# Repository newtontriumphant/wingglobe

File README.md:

# WingGlobe

Quick Link Tree:

* [I. Introduction!](#i-introduction)
* [II. About This Project - Why I Chose To Make It!](#ii-about-this-project---why-i-chose-to-make-it)
* [III. About This Project - What Is It?!](#iii-about-this-project---what-is-it)
* [IV. Project Images And Technical Documentation!](#iv-project-images-and-technical-documentation)
* [V. Notes For Reviewers!](#v-notes-for-reviewers)
* [VI. Final Remarks!](#vi-final-remarks)
  
## I. Introduction!

Heyo! Thanks for reviewing my project! I'm **zsharpminor** (a.k.a. funkeudo), co-creator of FiddleStein, and this is WingGlobe, which is a (TL;DR) fully autonomous Weather-Telling Snow Globe with a custom propulsion mechanism, PWM control, backlighting, E-INK display, support for my existing ecosystem of temperature sensors, and a changeable theme. This project is being created with the support of Hack Club Blueprint, and it is an entry for Blueprint's 7-day Christmas-Themed Project Competition. I am aiming for this to be a **Tier 3** project (see section at the very end of this README for justification).

(Disclaimer: the above image is a **render**, this project is not actually built yet; CAD screenshots can be found in section IV).

**IMPORTANT REVIEWER'S NOTE:** there is a section at the **end** of this README.md file, please read through it before returning this project if possible :)

My BOM.csv is in the parent directory, additionally a link to my online BOM is https://docs.google.com/spreadsheets/d/1PTxZxDy7cq01-oPVpPEEbVuQKtVb_WSBa-1fNMrsmt8/. Thanks! :3

Before I get into why I made this project, I would like to extend a huge thanks to can can't aka kleigh (my hero), as well as sam, alex, zach, renran, deven, paolo, john cohn, olive, my teammates Max & Sidd, tanuki, nathan, everyone from AMD, and every single other equally important person that made Blueprint & Prototype happen - I literally found out about Blueprint (and Hack Club itself!) only a month and a week ago, finished a few projects and became a reviewer one week later, had the most fun I've _ever_ had at Prototype, as well as inspired myself to get back into hardware, and re-dedicate my life to electronics. I really appreciate everything each and every one of you has done, and, without further ado, here's why WingGlobe exists.

## II. About This Project - Why I Chose To Make It!

You're probably looking at this and asking me "why the hell would you make a smart snow globe?!" The answer is a bit more complex than you think!

To start off with, I'm going to say quite bluntly that this project wouldn't exist without the Blueprint Christmas Competition. Even though I've worked with hardware for years, got HM with a self playing violin, and have been a Blueprint reviewer for over a month, I **don't actually own a 3D printer** (I've been using my local library's for all of my past projects so far)! I was planning on buying one a few weeks ago, then I set myself the challenge of getting one through Blueprint by reviewing a lot and getting tickets - but my current pace is rather lackluster. In addition, I needed ideas for projects to build - Blueprint is awesome because you can ship literally anything you can imagine, as long as it's under a certain dollar amount; but I was facing a bit of a creative block until this competition came about! My first project idea was to make a laser projecting 2026 New Year's countdown - but then I remembered that New Years would be over by the time this project would be built! My goal with WingGlobe was to make a project that, while Christmas-themed, **doesn't rely on Christmas to exist** and can be used **at any time of the year**! (Christmas in July, anyone?)

Additionally, I've made an ecosystem of projects (including one that I made through Blueprint - my SmartBell!) that feature temperature and humidity sensors. I wanted them to seamlessly work together wirelessly somehow, and needed a way to make that possible. That is also the main reason I chose the ESP32-S3 for this project, besides the fact that I already owned one, that it would cut PCBA cost in half, and that it would require one less parcel to be shipped.

Finally, I've been interested in weather and meteorology in general for a few years now, and I always wanted a weather station that relied on multiple sources of data that I myself provide, in addition to the commercial weather reports available.

The Snow Globe that builds this project's core features an empty space for _any_ 3d model or figurine (assuming it's heavy enough to withstand the fan blowing snow around it!) - and I've chosen a Christmas-themed one for my first few months with WingGlobe to fit the competition's theme.

Finally, if you're wondering why it's called WingGlobe, it's a reference to aviation, where meteorology is key (bad name, I know, but it stuck!)

I wanted WingGlobe to fit these criteria:

* It **must** be overwhelmingly Christmas-themed.
* It **must** have a decent amount of hardware complexity.
* It **must** be usable outside of just Christmas season.
* It **must** predominantly integrate CAD and software instead of being _just_ hardware.
* It **must** be actually useful in everyday life.
* The PCB **must** be under 100x100mm, eligible for GSDL, and Economic PCBA.
* All parts of the project **must** be printable on the Bambu A1 Mini with minimal supports and t*nkering.

I think I did a pretty good job fitting these criteria, if I do say so myself. Anyways, enough yapping, here's what the project actually _does_:

## III. About This Project - What Is It?!

WingGlobe is basically a glorified weather report station powered by a SEEED Studios XIAO ESP-32-S3 (that I already own - more on that in Section V) that runs 16 addressable SK6812-MINI LEDs, as well as an onboard temp/humi/pressure sensor and a MOSFET powering a 4010 fan with PWM control. When the weather shifts, the snow globe is updated to match - calm weather is a white / light-blue gradient and no fan power, sunny weather is a yellow / light red gradient, sunrise and sunset are adapted to red / orange gradients, and during the night, the snow globe will be engulfed in a replica of the aurora borealis (clear sky) or simply white / dark blue (cloudy sky). The real fun begins when it rains! When the winds start, the 4010 fan's PWM controller starts to rev it up - the more dangerous the wind, the more the little snow in the globe will swirl around! I am planning to use lightweight cotton / styrofoam blend beads to imitate snow (my original idea of 3D printing them sadly failed), as well as a custom mesh that stops them from breaking the fan or going out of the top of the globe. WingGlobe's E-Ink can be customized with a touch pad on WingGlobe's PCB to show varying levels of information from varying sensors. Additionally, the fan and LEDs can be turned off with a switch on WingGlobe's side when not needed (i.e. overnight).

WingGlobe seamlessly integrates with my SmartBell, moonboard, ADS-B stations, and BarnSense projects to provide up to three different simultaneous readings of temperature, humidity, and pressure. WingGlobe also has a built-in sensor for indoor temperature and humidity (should be quite useful next to my soon-to-be 3D Printer!) For now, WingGlobe relies on commercially available data for wind readings, but I hope to create another project soon so that everything can be run off the grid and without requiring any API.

WingGlobe's ESP32-S3 connects via ESP-NOW and WiFi to fetch data from my close and far stations, respectively. You're halfway there, have a cookie! 🍪

## IV. Project Images And Technical Documentation!

### SCHEMATIC:

### PCB:

### CAD:

(base, with cutouts for PCB, fan, and globe)

(top, made to be glued onto base)

### CAD WITH PCB:

(top view)

(side view)

(bottom view)

(top - birds-eye view without lid)

### ASSEMBLED PRODUCT:

(Front - Angle One)

(Front - Angle Two)

(Top)

(Side)

(Bottom)

### CARTS:

(AliExpress Checkout)

(JLCPCB PCB Options)

(JLCPCB PCBA 1)

(JLCPCB PCBA 2)

(JLCPCB PCBA 3)

(JLCPCB Pre-Discounts)

(JLCPCB Final Checkout As Shown On BOM)

**NOTE**: My name was redacted using the Inspect Element tool as this repository is publically visible. If an unredacted screenshot is required, please DM me or return my project.

### I will self-fund the E-INK display due to the project tier being bumped down to T4.

### RENDER:

(My friend with Blender skills did this and it turned out amazing, so I'm making this my cover image!)

## V. Notes For Reviewers!

### Usage Of Pre-Built Devboard:

I chose to use the XIAO ESP32-S3 over making a custom ESP32 or RP2040 devboard base for three reasons:

1. I already own quite a few ESP32-S3s, making an ESP32 from scratch would more than **double** the PCBA cost at JLC, and make my order **ineligible** for GSDL shipping, which would push my budget to Tier 2.
2. I've already made a devboard, I know the hassles that are involved in wiring and routing, and I did not want to miss a single decoupling capacitor and risk my board being browned out.
3. I wanted to spend more time polishing software and CAD, and using a pre-built devboard gave me that opportunity.

Again, if this cannot be approved for Tier 3 due to a lack of complexity, I understand, and will remove parts to bring the budget down to a Tier 4.

### Why Are You Requesting Six Snow Globes?

Because it's the cheapest option available for a half-decent snowglobe on AliExpress. The next-cheapest was $7 for two, and I preferred to get six for $6.88.

All of my costs are optimized as **much as possible**, I'm using AliExpress for my items, and I've done my best to keep it in budget.

### Why Are You Requesting $10 More Than You Need For JLCPCB?

JLCPCB has a $10 coupon for PCBA (scroll up to the images section for proof). Said coupon expires in 2 days, and, knowing HCB, it will take more than 2 days to process this grant. If another coupon appears, I will return the difference immediately.

### "ThIs ReADmE iS AI gEnEraTEd!"

No, no it's not. I know how to use markdown, and I'll even occasionally use an em-dash—like so. That doesn't necessarily mean my README is automatically AI. Zero AI was used in the making of this project, and writing this text-heavy README alone took me two hours. If you need proof, I can provide a screen recording!

That's all, thanks! :D

## VI. Final Remarks!

Please ping or DM me on Slack (@zsharpminor) if you have any questions regarding my project.

Thank you so much for taking your precious time to read all the way through this extremely long README (I wanted to be well documented, okay?!)

You get a massive slice of vanilla cheesecake! :D 🍰

P.S. Happy New Year!!! I worked on this project literally as the clock struck 12 - I have a journal entry to prove it :)

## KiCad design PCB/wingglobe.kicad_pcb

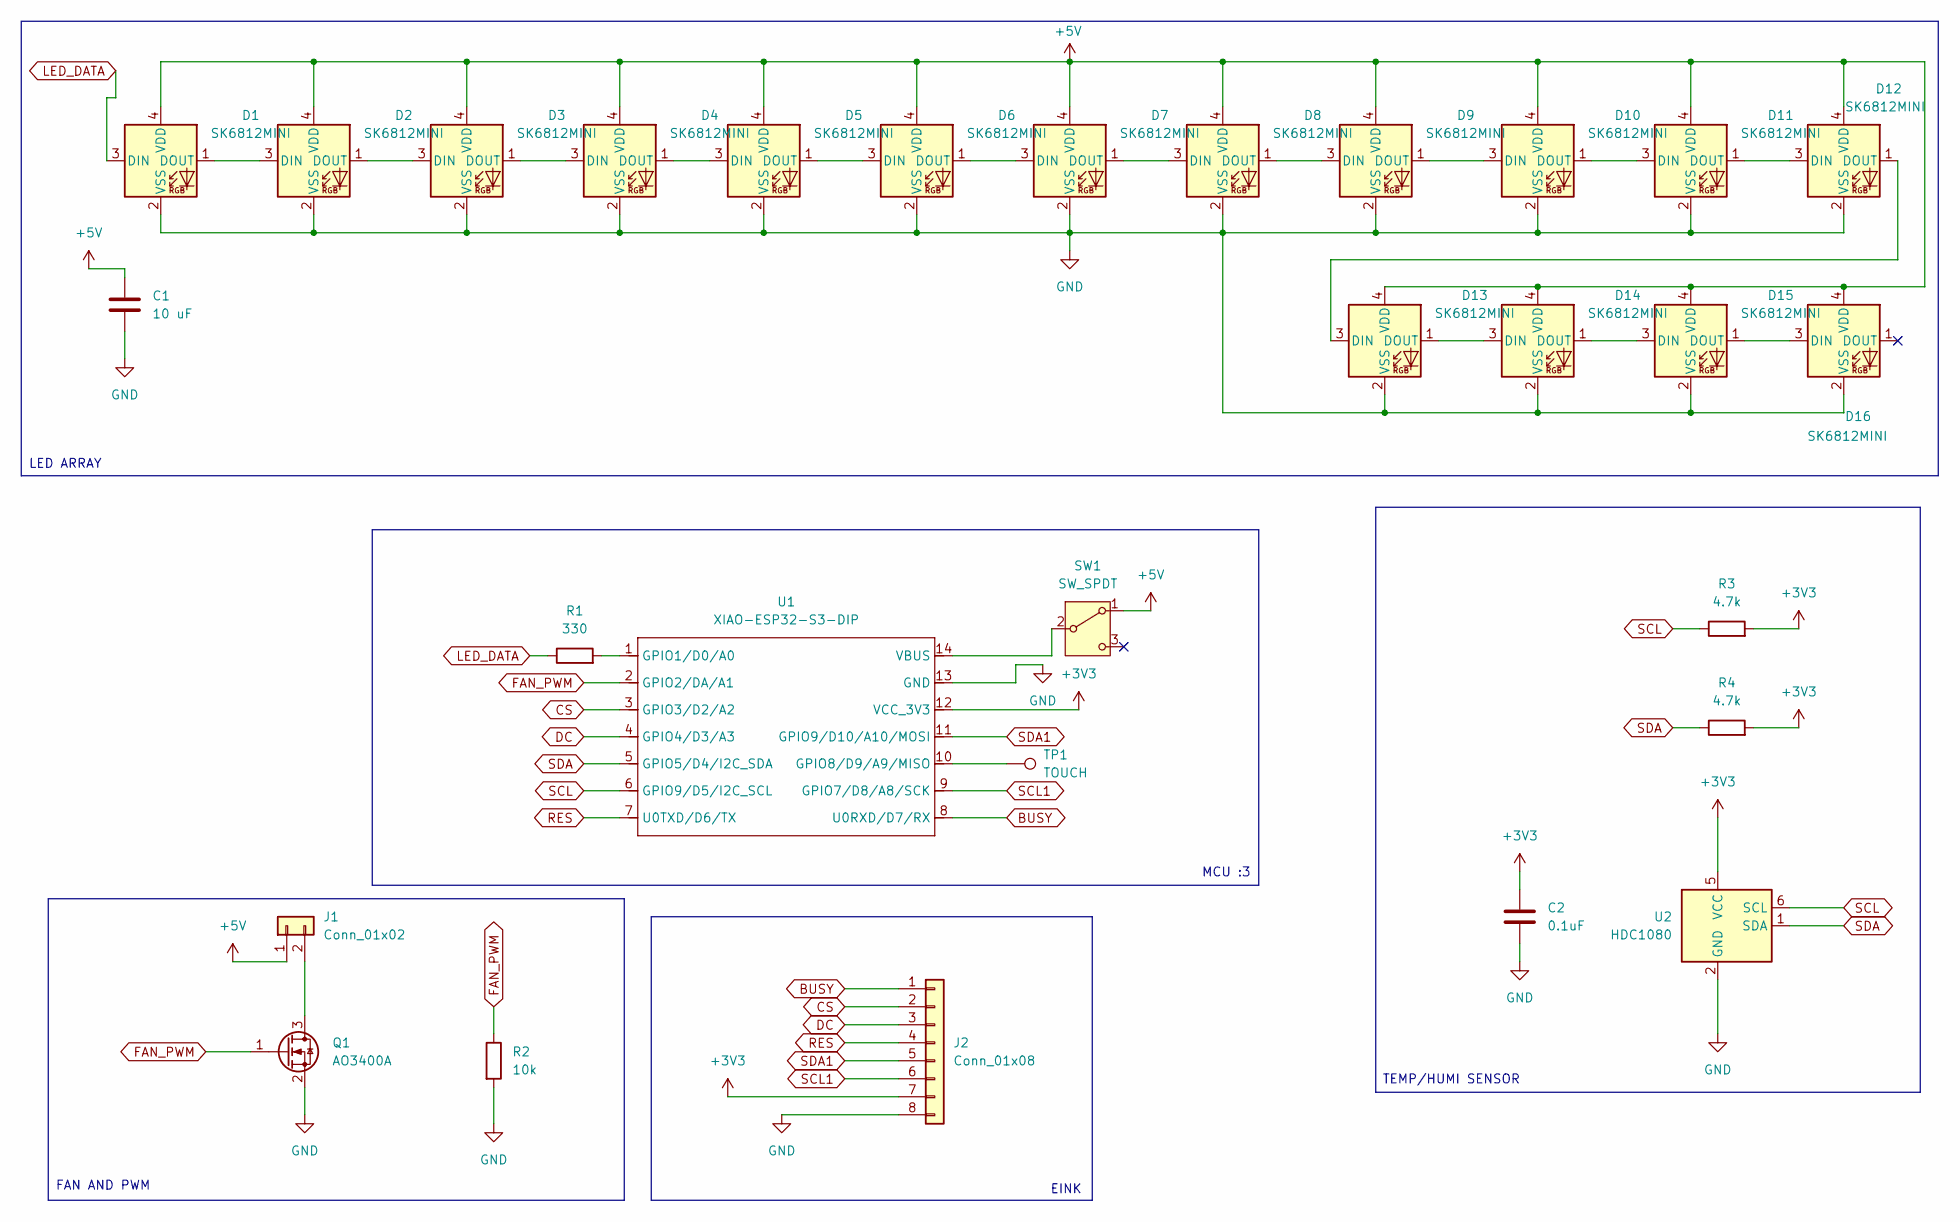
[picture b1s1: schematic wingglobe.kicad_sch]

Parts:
C1: 10 uF; C_0402_1005Metric
C2: 0.1uF; C_0402_1005Metric
D1, D2, D3, D4, D5, D6, D7, D8, D9, D10, D11, D12, D13, D14, D15, D16: SK6812MINI; LED_SK6812MINI_PLCC4_3.5x3.5mm_P1.75mm
J1: Conn_01x02; JST_XH_B2B-XH-A_1x02_P2.50mm_Vertical
J2: Conn_01x08; PinHeader_1x08_P2.54mm_Vertical
Q1: AO3400A; SOT-23
R1: 330; R_0402_1005Metric
R2: 10k; R_0402_1005Metric
R3, R4: 4.7k; R_0402_1005Metric
SW1: SW_SPDT; SW_Slide_SPDT_Angled_CK_OS102011MA1Q
TP1: TOUCH; TestPoint_Pad_D4.0mm
U1: XIAO-ESP32-S3-DIP; XIAO-ESP32S3-DIP
U2: HDC1080; Texas_PWSON-N6

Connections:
+3V3: C2.1, J2.7, R3.2, R4.2, U1.12 (VCC_3V3), U2.5 (VCC)
+5V: C1.1, D1.4 (VDD), D2.4 (VDD), D3.4 (VDD), D4.4 (VDD), D5.4 (VDD), D6.4 (VDD), D7.4 (VDD), D8.4 (VDD), D9.4 (VDD), D10.4 (VDD), D11.4 (VDD), D12.4 (VDD), D13.4 (VDD), D14.4 (VDD), D15.4 (VDD), D16.4 (VDD), J1.1, SW1.1 (A)
BUSY: J2.1, U1.8 (U0RXD/D7/RX)
CS: J2.2, U1.3 (GPIO3/D2/A2)
DC: J2.3, U1.4 (GPIO4/D3/A3)
FAN_PWM: Q1.1 (G), R2.1, U1.2 (GPIO2/DA/A1)
GND: C1.2, C2.2, D1.2 (VSS), D2.2 (VSS), D3.2 (VSS), D4.2 (VSS), D5.2 (VSS), D6.2 (VSS), D7.2 (VSS), D8.2 (VSS), D9.2 (VSS), D10.2 (VSS), D11.2 (VSS), D12.2 (VSS), D13.2 (VSS), D14.2 (VSS), D15.2 (VSS), D16.2 (VSS), J2.8, Q1.2 (S), R2.2, U1.13 (GND), U2.2 (GND)
LED_DATA: D1.3 (DIN), R1.1
unnamed: D1.1 (DOUT), D2.3 (DIN)
unnamed: D2.1 (DOUT), D3.3 (DIN)
unnamed: D3.1 (DOUT), D4.3 (DIN)
unnamed: D4.1 (DOUT), D5.3 (DIN)
unnamed: D5.1 (DOUT), D6.3 (DIN)
unnamed: D6.1 (DOUT), D7.3 (DIN)
unnamed: D7.1 (DOUT), D8.3 (DIN)
unnamed: D8.1 (DOUT), D9.3 (DIN)
unnamed: D9.1 (DOUT), D10.3 (DIN)
unnamed: D10.1 (DOUT), D11.3 (DIN)
unnamed: D11.1 (DOUT), D12.3 (DIN)
unnamed: D12.1 (DOUT), D13.3 (DIN)
unnamed: D13.1 (DOUT), D14.3 (DIN)
unnamed: D14.1 (DOUT), D15.3 (DIN)
unnamed: D15.1 (DOUT), D16.3 (DIN)
unnamed: J1.2, Q1.3 (D)
unnamed: SW1.2 (B), U1.14 (VBUS)
unnamed: R1.2, U1.1 (GPIO1/D0/A0)
unnamed: TP1.1, U1.10 (GPIO8/D9/A9/MISO)
RES: J2.4, U1.7 (U0TXD/D6/TX)
SCL: R3.1, U1.6 (GPIO9/D5/I2C_SCL), U2.6 (SCL)
SCL1: J2.6, U1.9 (GPIO7/D8/A8/SCK)
SDA: R4.1, U1.5 (GPIO5/D4/I2C_SDA), U2.1 (SDA)
SDA1: J2.5, U1.11 (GPIO9/D10/A10/MOSI)

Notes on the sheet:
TEMP/HUMI SENSOR
FAN AND PWM
EINK
MCU :3
LED ARRAY

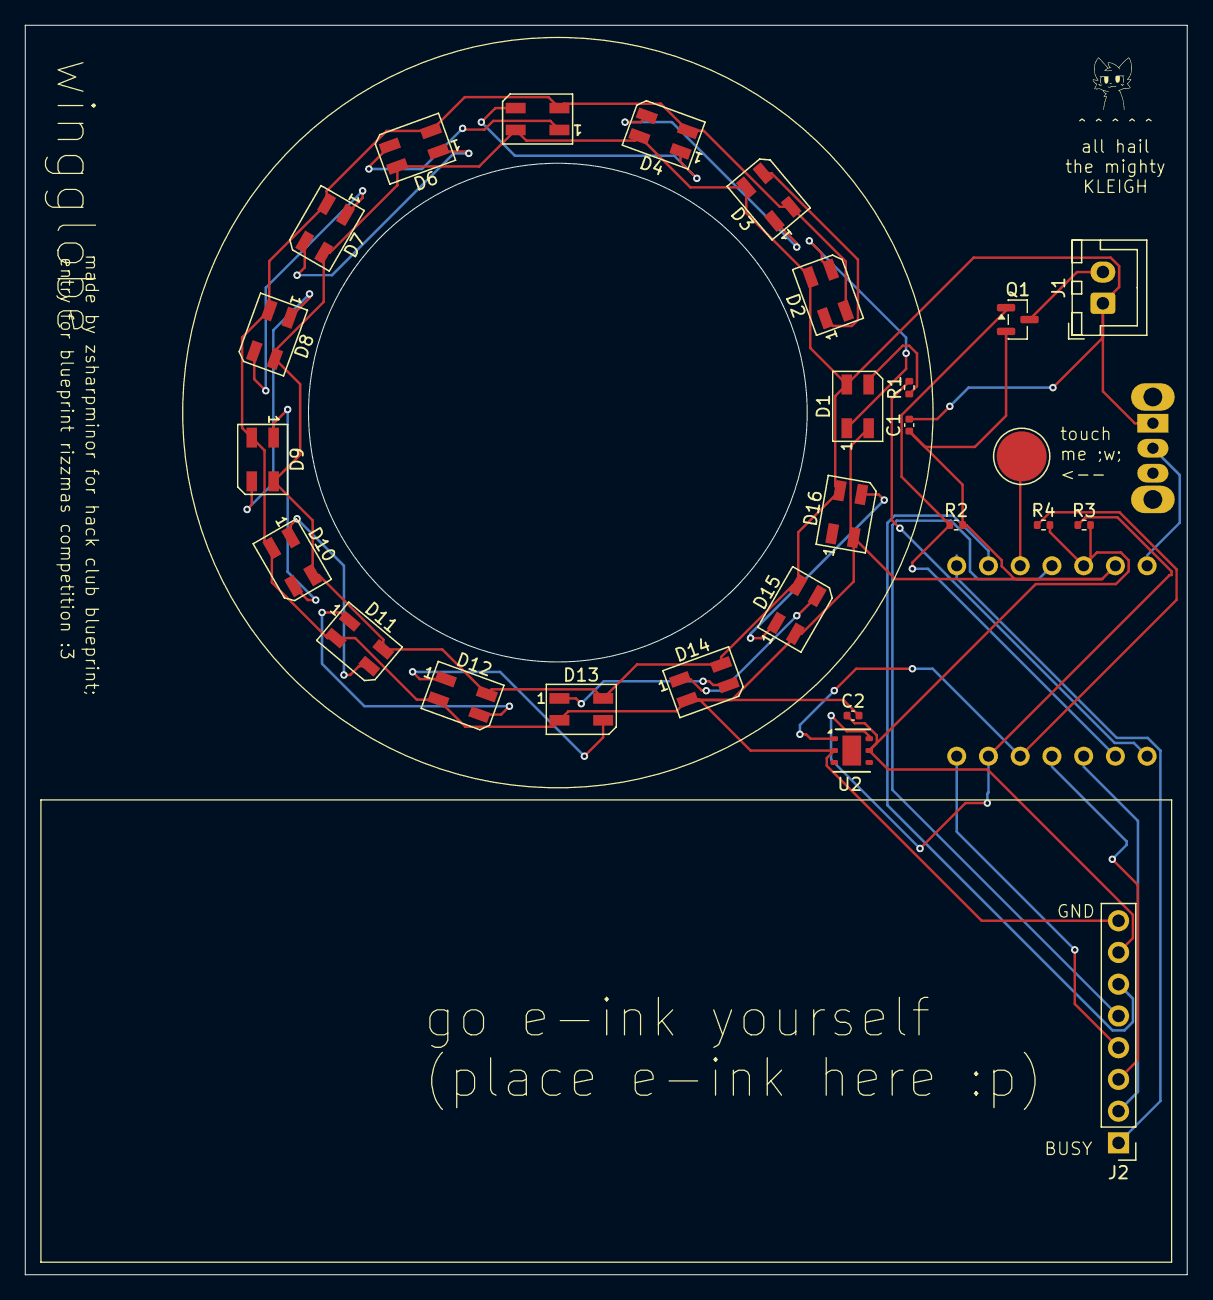
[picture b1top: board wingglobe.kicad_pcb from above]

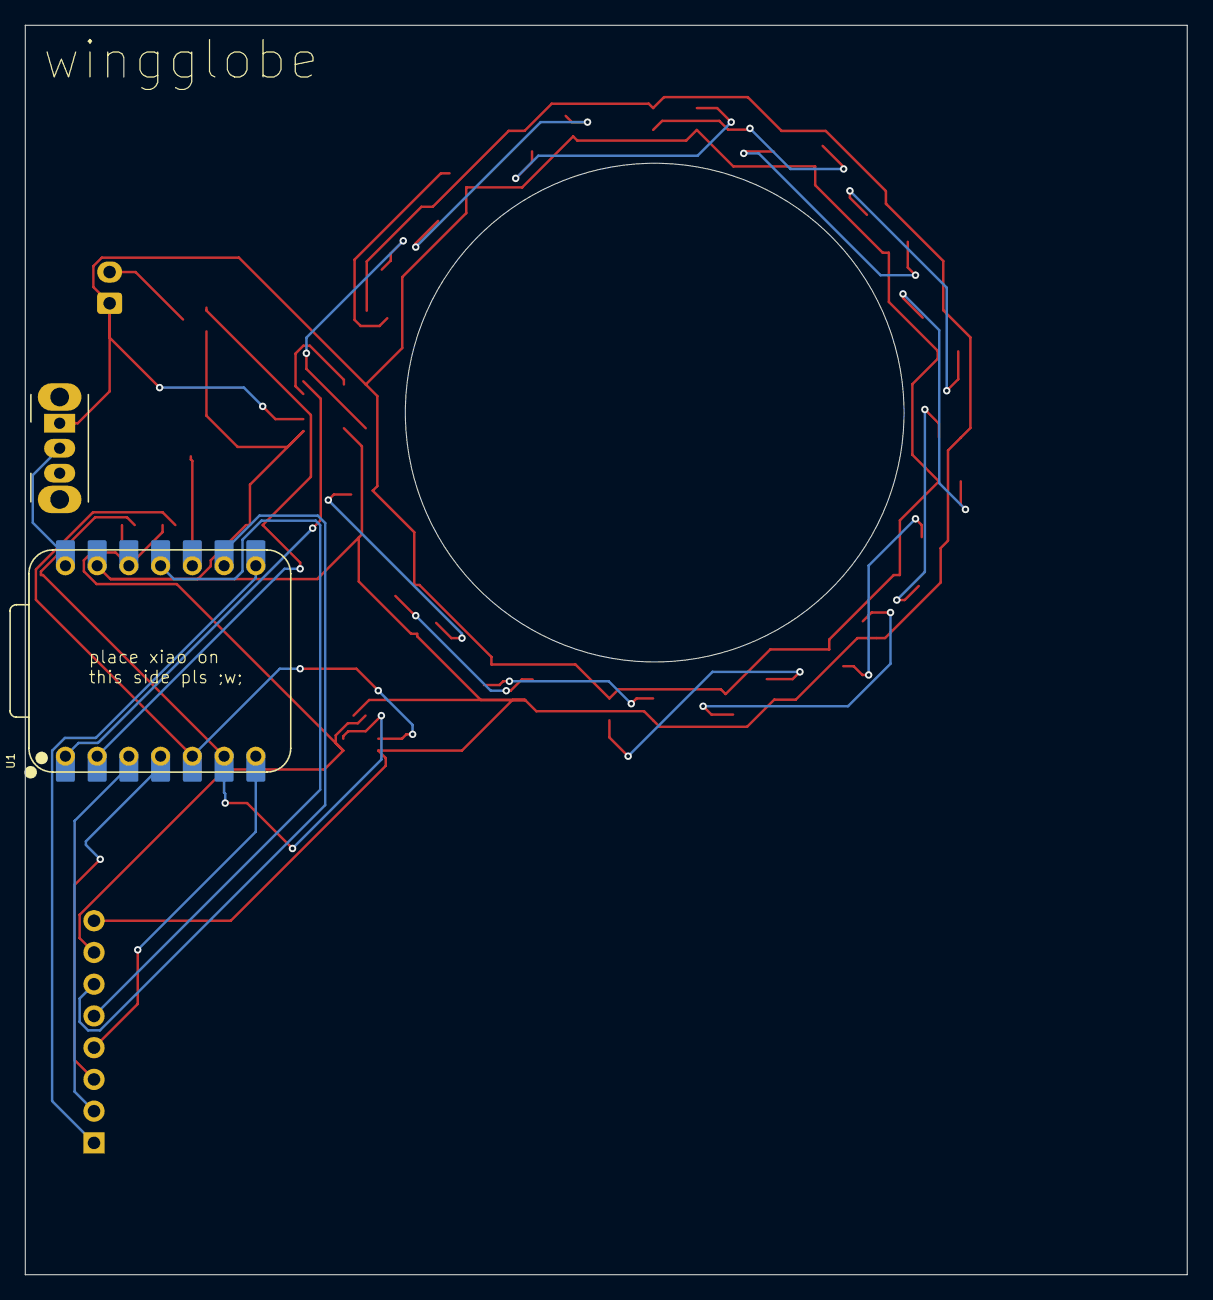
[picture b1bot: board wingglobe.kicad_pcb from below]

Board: 2 copper layers, 93.0 x 100.0 mm, 29 parts (2 on the bottom side), 32 nets.

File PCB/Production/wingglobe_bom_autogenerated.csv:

Designator,Footprint,Quantity,Value,LCSC Part #
C1,0402,1,10 uF,
C2,0402,1,0.1uF,
"D1, D10, D11, D12, D13, D14, D15, D16, D2, D3, D4, D5, D6, D7, D8, D9",LED_SK6812MINI_PLCC4_3.5x3.5mm_P1.75mm,16,SK6812MINI,
J1,JST_XH_B2B-XH-A_1x02_P2.50mm_Vertical,1,Conn_01x02,
J2,PinHeader_1x08_P2.54mm_Vertical,1,Conn_01x08,
Q1,SOT-23,1,AO3400A,
R1,0402,1,330,
R2,0402,1,10k,
"R3, R4",0402,2,4.7k,
SW1,SW_Slide_SPDT_Angled_CK_OS102011MA1Q,1,SW_SPDT,
TP1,TestPoint_Pad_D4.0mm,1,TOUCH,
U1,XIAO-ESP32S3-DIP,1,XIAO-ESP32-S3-DIP,
U2,Texas_PWSON-N6,1,HDC1080,

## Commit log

2026-01-01 Finalized README.md.
    god ts took a while
2026-01-02 Add BOM.csv
2026-01-02 Create temp
2026-01-02 Added Full Housing Files
2026-01-02 Added Top Housing Files
2026-01-02 Added Bottom Housing Files
2026-01-02 Added Assembled Files
2026-01-02 Added All Final CAD Files
2026-01-02 Added All KiCad Files
2026-01-02 Added All Production Files And Gerbers
2026-01-02 Added All Final PCB Files
2026-01-02 Added Final Code
2026-01-02 Added All Final Code
2026-01-05 Fixed README.MD
    Removed justification for project tier and added note about self-funding the E-INK display.
2026-01-05 Fixed BOM.csv
    Updated BOM with new item prices and totals.
2026-01-05 Update BOM.csv with new formatting and data
